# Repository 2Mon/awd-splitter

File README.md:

# awd-splitter
105c rated AWD splitter pcb for 3d printers

I needed a simpler way to wire up AWD printers, so I decided to make a simple AWD splitter PCB. instead of running 12 sets of wires, 4 for motors and 8 for fans and thermistors, this means you only need to run two big 16 channel wires down to your electronics bay. On the other end of the big wires, you can just use another one of these PCBs to break it back out and connect it to your mainboard, or just crimp individual connectors on the other end. This supports four motors for AWD, as well as a thermistor and cooling fan for each. It is rated to 105c chamber temps (limited by the connectors) but could likely go higher if needed. 

To use this project, solder the connectors onto the top side of the board. Crimp your motor wires and plug them into the motor ports. Take a 16 pin connector and wire it down to your electronics bay. Do the same for the thermistors and fans if desired. 

The PCB itself is very simple, but I tried to keep it fairly compact so it can fit easily anywhere on a printer. It uses Molex Nanofit connectors for high temp resistance and ease of crimping. 

^^ wiring info also printed on PCB!

| Item                  | Price ($) | Quantity | Total ($) | Link |
|-----------------------|-----------|----------|-----------|------|
| Nanofit 2x8           | 4.60      | 4        | 18.40     | https://www.digikey.com/en/products/detail/molex/1053101216/6164149? |
| Nanofit 1x4           | 1.11      | 8        | 8.88      | https://www.digikey.com/en/products/detail/molex/1053091204/6131609? |
| Nanofit 1x2           | 0.95      | 16       | 15.20     | https://www.digikey.com/en/products/detail/molex/1053091202/6131607? |
| Nanofit 2x8 connector | 0.98      | 4        | 3.92      | https://www.digikey.com/en/products/detail/molex/1053081216/6164114? |
| Nanofit 1x4 connector | 0.41      | 8        | 3.28      | https://www.digikey.com/en/products/detail/molex/1053071204/6131602? |
| Nanofit 1x2 connector | 0.35      | 16       | 5.60      | https://www.digikey.com/en/products/detail/molex/1053071202/6131600? |
| Crimp                 | 0.11      | 140      | 15.4      | https://www.digikey.com/en/products/detail/molex/1053002100/7693143? |
| PCB                   | 3.60      | 1        | 3.60      | JLCPCB |

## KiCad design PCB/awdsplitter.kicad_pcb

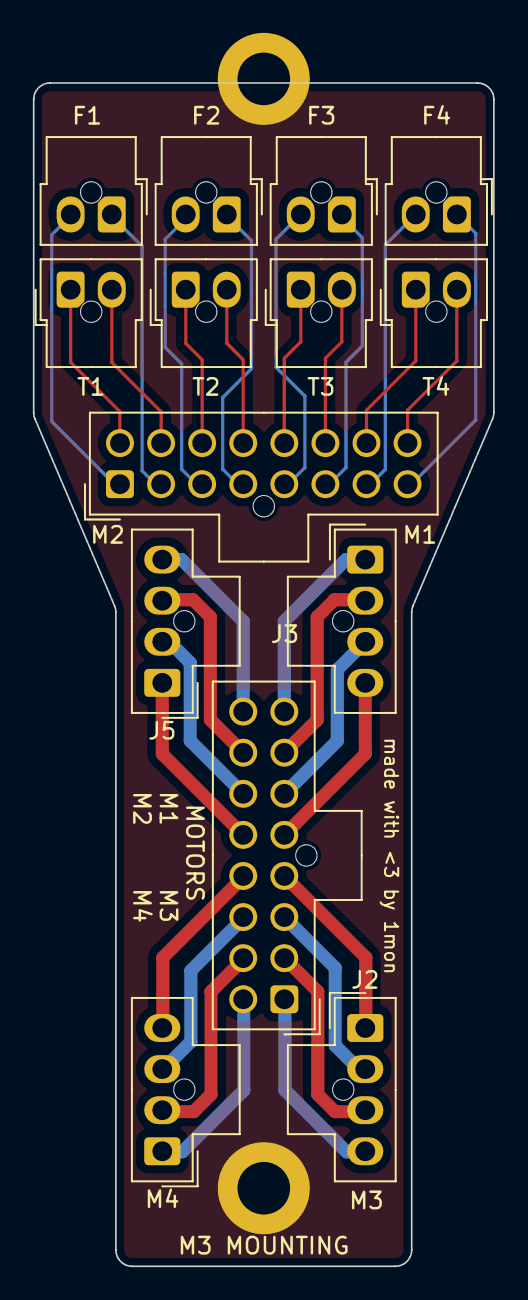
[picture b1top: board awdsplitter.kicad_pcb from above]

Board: 2 copper layers, 28.0 x 72.0 mm, 16 parts (0 on the bottom side), 33 nets.

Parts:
F1, F2, F3, F4: MICROFIT_1x2_THT_V; Molex_Nano-Fit_105309-xx02_1x02_P2.50mm_Vertical
J1, J8: MICROFIT_2x8_THT_V; Molex_Nano-Fit_105310-xx16_2x08_P2.50mm_Vertical
J2, J5: MICROFIT_1x4_THT_V; Molex_Nano-Fit_105309-xx04_1x04_P2.50mm_Vertical
M1, M4: MICROFIT_1x4_THT_V; Molex_Nano-Fit_105309-xx04_1x04_P2.50mm_Vertical
M3 MOUNTING, M3 MOUNTING#2: MountingHole_Pad; MountingHole_3.2mm_M3_DIN965_Pad
T1, T2, T3, T4: MICROFIT_1x2_THT_V; Molex_Nano-Fit_105309-xx02_1x02_P2.50mm_Vertical

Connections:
/F1 +: F2.2, J8.3
/F1 -: F2.1, J8.4
/F2 +: F4.2, J8.7
/F2 -: F4.1, J8.8
/F3 +: J8.11, T2.1
/F3 -: J8.12, T2.2
/F4 +: J8.15, T4.1
/F4 -: J8.16, T4.2
/M1 A+: J1.1, J2.4
/M1 A-: J1.2, J2.3
/M1 B+: J1.3, J2.2
/M1 B-: J1.4, J2.1
/M2 A+: J1.5, M1.4
/M2 A-: J1.6, M1.3
/M2 B+: J1.7, M1.2
/M2 B-: J1.8, M1.1
/M3 A+: J1.9, M4.1
/M3 A-: J1.10, M4.2
/M3 B+: J1.11, M4.3
/M3 B-: J1.12, M4.4
/M4 A+: J1.13, J5.1
/M4 A-: J1.14, J5.2
/M4 B+: J1.15, J5.3
/M4 B-: J1.16, J5.4
/T1 A: F1.2, J8.1
/T1 B: F1.1, J8.2
/T2 A: F3.2, J8.5
/T2 B: F3.1, J8.6
/T3 A: J8.9, T1.1
/T3 B: J8.10, T1.2
/T4 A: J8.13, T3.1
/T4 B: J8.14, T3.2
GND: M3 MOUNTING.1, M3 MOUNTING#2.1

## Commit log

2026-02-20 add readme
    readme
2026-02-20 Create PCB
2026-02-20 add bom
2026-02-20 Update AWD_BOM.csv with new item entries
2026-02-20 Update Crimp connector pricing and link
2026-02-20 Update PCB price and quantity in README
    Updated PCB price and quantity in the connector table.
2026-02-20 Modify item prices and quantities in AWD_BOM.csv
    Updated prices and quantities for items in the BOM.
